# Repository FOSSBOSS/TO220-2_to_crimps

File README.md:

# TO220-2_to_crimps
Through hole TO-220 to 1/4 spade connectors adapter. intent is to have JLPB or PCB way create the parts I need. <br>
<br>
https://www.digikey.com/en/models/2170998  
<br>
https://www.sensata.com/products/temperature/6700-series-220-subminiature-thermostat
<br><br>

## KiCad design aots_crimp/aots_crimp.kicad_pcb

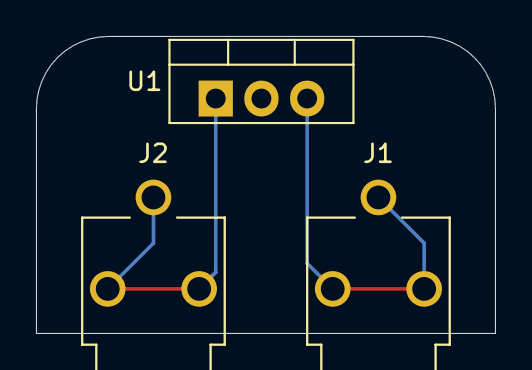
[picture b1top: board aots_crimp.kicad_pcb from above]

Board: 2 copper layers, 25.5 x 16.5 mm, 3 parts (0 on the bottom side), 2 nets.

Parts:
J1, J2: 4910; KEYSTONE_4910
U1: AOTS; TO-220-3_Vertical

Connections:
unnamed: J2.1_1, J2.1_2, J2.1_3, U1.1 (ADJ)
unnamed: J1.1_1, J1.1_2, J1.1_3, U1.3 (VI)
